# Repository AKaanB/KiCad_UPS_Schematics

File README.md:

# KiCad_UPS_Schematics
 Open Source Schematics of a Li-ion battery based 1.1 KW uninterruptible power supply. Design consists of CC/CV Charger and passive battery balancing and a full bridge inverter.
You can just take a look at the PDF if you only want to see the schematics.

All parts have footprints except the transformers. 
Order list is finished. All parts can be bought from digikey they are included in the table.

This design is NOT tested. I will update it if I can finish it.

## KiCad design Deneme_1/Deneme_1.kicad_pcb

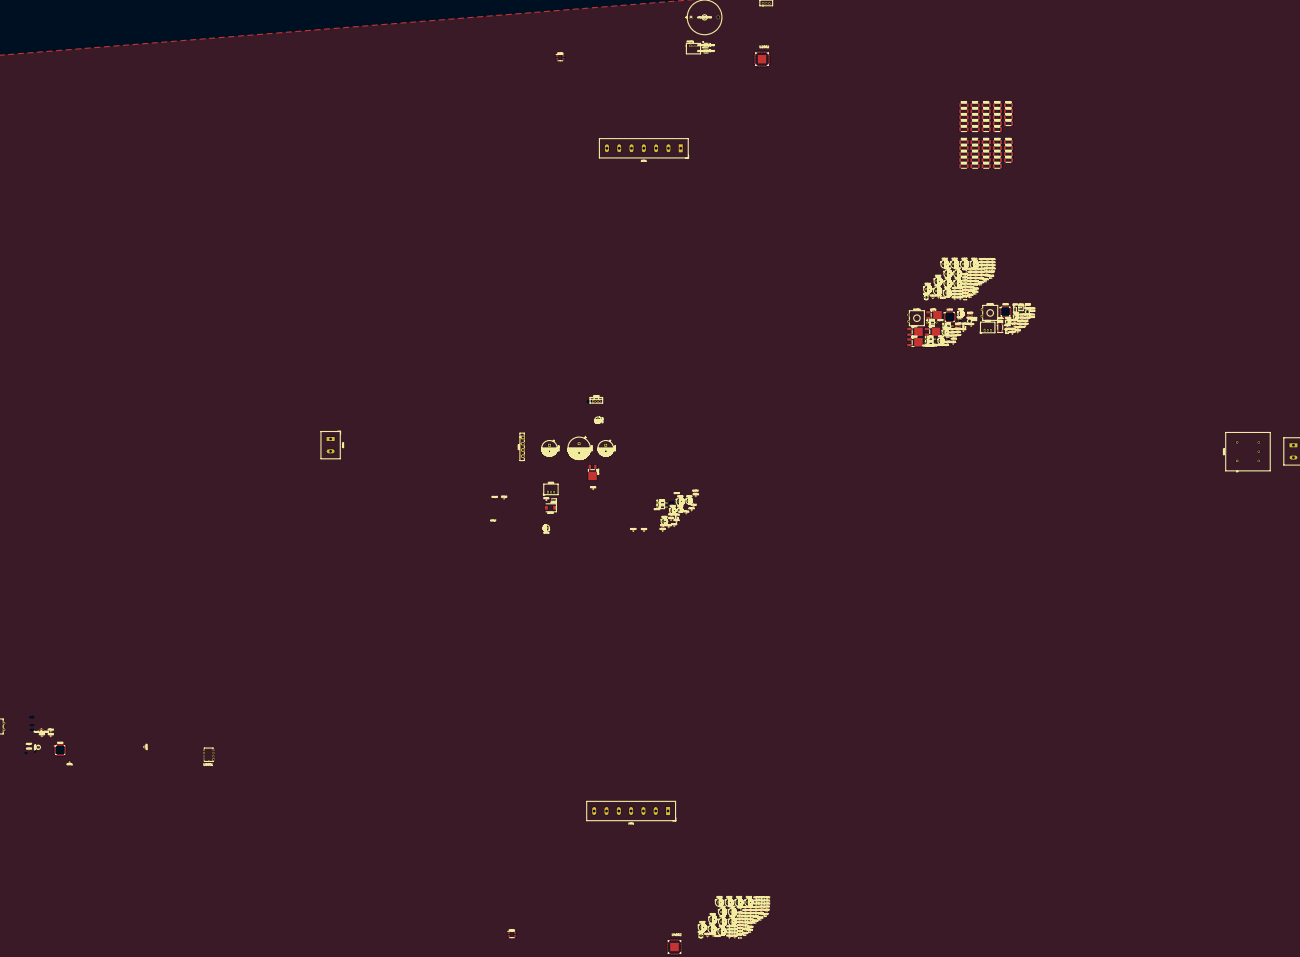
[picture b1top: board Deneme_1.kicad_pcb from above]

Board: 2 copper layers, 329 parts (0 on the bottom side), 230 nets, no tracks yet.

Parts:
C2001, C2002, C4001, C4002: 47nF_16V; C_0603_1608Metric_Pad1.05x0.95mm_HandSolder
C2003, C2007, C2008, C3001, C3007, C4003, C4007, C4008, C5021: 100nF_50V; C_0603_1608Metric_Pad1.05x0.95mm_HandSolder
C2004, C4004: 2uF2_16V; C_0603_1608Metric_Pad1.05x0.95mm_HandSolder
C2005, C4005: 10uF_10V; C_0603_1608Metric_Pad1.05x0.95mm_HandSolder
C2006, C4006: 1nF_10V; C_0603_1608Metric_Pad1.05x0.95mm_HandSolder
C2009, C3010, C3011, C3012, C3013, C3014, C4009, C5001, C5003, C5012, C6001, C6002, C6006: 100nF_10V; C_0603_1608Metric_Pad1.05x0.95mm_HandSolder
C2010, C2011, C4010, C4011: 2uF2_50V; C_0603_1608Metric_Pad1.05x0.95mm_HandSolder
C2012, C2013, C2014, C2015, C2016, C2017, C2018, C2019, C2020, C2021, C2022, C2023, C4012, C4013, C4014, C4015, C4016, C4017, C4018, C4019, C4020, C4021, C4022, C4023: 0.1uF_50V; CP_Radial_D6.3mm_P2.50mm
C3002, C3003: 20p_10V; C_0402_1005Metric
C3004, C3005: 4.7pF_10V; C_0402_1005Metric
C3006: 10uF_10V; CP_Radial_D4.0mm_P1.50mm
C3008: 100n_10V; C_0603_1608Metric_Pad1.05x0.95mm_HandSolder
C3009, C5022: 1uF_50V; CP_Radial_D4.0mm_P1.50mm
C5002, C5010: 4.7u_25V; CP_Radial_D5.0mm_P2.50mm
C5004: 10n_25V; C_0603_1608Metric_Pad1.05x0.95mm_HandSolder
C5005: 27u_50V; CP_Radial_D5.0mm_P2.00mm
C5006, C5007, C6003, C6004: 20pF_10V; C_0402_1005Metric
C5008, C5020, C6005, C6009, C6014, C6015, C6018: 100n_25V; C_0201_0603Metric
C5009: 2m2_63V; CP_Radial_D18.0mm_P7.50mm
C5011, C5013: 470u_63V; CP_Radial_D12.5mm_P5.00mm
C5014, C6010: 10nF_10V; C_0603_1608Metric_Pad1.05x0.95mm_HandSolder
C5015, C6011: 1uF_10V; C_0603_1608Metric_Pad1.05x0.95mm_HandSolder
C5016, C5019: 10u_50V; CP_Radial_D5.0mm_P2.50mm
C5017, C6012: 100n_50V; C_0201_0603Metric
C5018: 47u_50V; CP_Radial_D6.3mm_P2.50mm
C6007, C6016: 10u_25V; CP_Radial_D5.0mm_P2.50mm
C6008, C6017: 47n_25V; C_0402_1005Metric
C6013: 4.7uF_25V; CP_Radial_D5.0mm_P2.50mm
D2001, D4001: LED; LED_D3.0mm
D2002, D2003, D2004, D2005, D2006, D2007, D4002, D4003, D4004, D4005, D4006, D4007: DZ2S051X0L; D_SOD-523
D3001, D5005: MMSZ4685T1G; D_SOD-123
D5001: GBU4B; Diode_Bridge_Vishay_GBU
D5002, D5003, D6001, D6002, D6003, D6004: 1N914; D_DO-35_SOD27_P7.62mm_Horizontal
D5004: S5AC-13-F; D_SMC
FL6001: FN405-10-02; Filter_Schaffner_FN405
Ferrit_Bead5001, Ferrit_Bead6001: R; R_0805_2012Metric_Pad1.15x1.40mm_HandSolder
J2001, J4001: Screw_Terminal_01x07; TerminalBlock_Dinkle_DT-55-B01X-07_P10.00mm
J3001, J5001, J6001: Conn_01x02; PinHeader_1x02_P1.27mm_Vertical
J3002: Conn_02x03_Counter_Clockwise; PinHeader_2x03_P1.27mm_Vertical
J3003: Conn_01x04; PinHeader_1x04_P1.27mm_Vertical
J5002, J6002: Screw_Terminal_01x02; TerminalBlock_Dinkle_DT-55-B01X-02_P10.00mm
L5001: AIRD-03-471K
PS6001: R-78B12-2.0; CONV_R-78B12-2.0
Q2001, Q4001: 2N7002; SOT-23
Q2002, Q2003, Q2004, Q2005, Q2006, Q2007, Q4002, Q4003, Q4004, Q4005, Q4006, Q4007: CSD16301Q2; Texas_DQK
Q5001, Q6001, Q6002, Q6003, Q6004: STD140N6F7; TO-252-2_TabPin1
R2001, R2006, R4001, R4006: 1k47; R_0603_1608Metric_Pad1.05x0.95mm_HandSolder
R2002, R2007, R4002, R4007: 1k82; R_0603_1608Metric_Pad1.05x0.95mm_HandSolder
R2003, R2004, R2005, R2009, R2010, R2011, R2012, R2013, R4003, R4004, R4005, R4009, R4010, R4011, R4012, R4013: 100; R_0603_1608Metric_Pad1.05x0.95mm_HandSolder
R2008, R3004, R3005, R4008: 100k; R_0402_1005Metric
R2014, R4014: 2.7k; R_0805_2012Metric_Pad1.15x1.40mm_HandSolder
R2015, R2016, R2017, R2018, R2019, R2020, R2021, R2022, R2023, R2024, R2025, R2026, R2027, R2028, R2029, R2030, R2031, R2032, R2033, R2034, R2035, R2036, R2037, R2038, R4015, R4016, R4017, R4018, R4019, R4020, R4021, R4022, R4023, R4024, R4025, R4026, R4027, R4028, R4029, R4030, R4031, R4032, R4033, R4034, R4035, R4036, R4037, R4038: 2.2; R_2512_6332Metric_Pad1.52x3.35mm_HandSolder
R2039, R2040, R2041, R2042, R2043, R2044, R3002, R4039, R4040, R4041, R4042, R4043, R4044: 1M; R_0603_1608Metric_Pad1.05x0.95mm_HandSolder
R2045, R2046, R2047, R2048, R2049, R2050, R2051, R2052, R2053, R2054, R2055, R2056, R3006, R3008, R4045, R4046, R4047, R4048, R4049, R4050, R4051, R4052, R4053, R4054, R4055, R4056, R5004, R5006, R5010: 1k; R_0603_1608Metric_Pad1.05x0.95mm_HandSolder
R3001, R5003: 3.3k; R_0805_2012Metric_Pad1.15x1.40mm_HandSolder
R3003, R5002, R5009, R5012, R6002, R6008: 10k; R_0603_1608Metric_Pad1.05x0.95mm_HandSolder
R3007, R3009, R5005, R5007: 2k; R_0805_2012Metric_Pad1.15x1.40mm_HandSolder
R5001, R6001, R6006: 22_2W; R_0603_1608Metric_Pad1.05x0.95mm_HandSolder
R5008, R5014: 33k; R_0603_1608Metric_Pad1.05x0.95mm_HandSolder
R5011: 500k; R_0603_1608Metric_Pad1.05x0.95mm_HandSolder
R5013: 5.6k; R_0402_1005Metric
R5015: 5k; R_0805_2012Metric_Pad1.15x1.40mm_HandSolder
R5016: 910k; R_0603_1608Metric_Pad1.05x0.95mm_HandSolder
R6003, R6005: 100k_5W; R_1210_3225Metric_Pad1.42x2.65mm_HandSolder
R6004, R6007: 10; R_0402_1005Metric
SW3001, SW5001, SW6001: SW_Push; SW_CW_GPTS203211B
TH2001, TH2002, TH4001, TH4002: ERT-J1VG103FA; R_0603_1608Metric_Pad1.05x0.95mm_HandSolder
U2001, U4001: ACS712ELCTR-30A-T; SOIC-8_3.9x4.9mm_P1.27mm
U2002, U4002: BQ76PL536APAPT; QFP50P1200X1200X120-65N
U3001: L7805CV; TO255P1040X460X1968-3
U3002, U5004: R-78C3.3-1.0; Converter_DCDC_RECOM_R-78E-0.5_THT
U3003: STM32F103C8Tx; LQFP-48_7x7mm_P0.5mm
U5001: IR2125PBF; DIP254P762X533-8
U5002, U6003: STM32F031K6Tx; LQFP-32_7x7mm_P0.8mm
U5003: SCD7812BTG; TO-220-3_Vertical
U6001, U6004: LTC7001EMSE#PBF; LTC7001EMSE-PBF
U6002, U6005: MCP1416; SOT-23-5
Y3001, Y5001, Y6001: AB308-8.000MHZ; Crystal_C38-LF_D3.0mm_L8.0mm_Vertical
Y3002: ABS25-32.768KHZ-6-T; Crystal_SMD_Abracon_ABS25-4Pin_8.0x3.8mm

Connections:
1_ADC_1: R5004.1, R5005.2, U5002.6
1_ADC_2: R5006.1, R5007.2, U5002.8
2_ADC_1: R3006.2, R3007.1, U3003.10
2_ADC_2: R3008.2, R3009.1, U3003.11
+BATT_1: C4003.1, C4012.1, D4002.1, J4001.7, R4016.2, R4051.2, U4001.3, U4001.4, U4002.52, U4002.53, U4002.54, U4002.55, U4002.56, U4002.57, U4002.58, U4002.59, U4002.63, U4002.64
+BATT_2: C2003.1, C2012.1, D2002.1, J2001.7, R2016.2, R2051.2, U2001.3, U2001.4, U2002.52, U2002.53, U2002.54, U2002.55, U2002.56, U2002.57, U2002.58, U2002.59, U2002.63, U2002.64
-BATT_1: C2003.2, C2004.2, C2005.2, C2006.2, C2008.2, C2009.2, C2011.2, C2017.2, C2018.2, C2019.2, C2020.2, C2021.2, C2022.2, C2023.2, C3001.2, C3002.2, C3003.2, C3004.2, C3005.2, C3006.2, C3007.2, C3008.1, C3009.2, C4003.2, C4004.2, C4005.2, C4006.2, C4008.2, C4009.2, C4011.2, C4017.2, C4018.2, C4019.2, C4020.2, C4021.2, C4022.2, C4023.2, C5002.2, C5004.2, C5006.1, C5007.1, C5009.2, C5010.2, C5011.2, C5012.2, C5013.2, C5014.2, C5015.2, C5016.2, C5017.2, C5018.2, C5019.2, C5020.2, C5021.2, C5022.2, C6003.1, C6004.1, C6005.2, C6006.2, C6008.2, C6010.2, C6011.2, C6012.2, C6013.2, C6014.2, C6015.2, C6017.2, D2007.2, D3001.2, D4007.2, D5001.4, D5004.2, D5005.2, FL6001.3, J2001.1, J3002.3, J3002.4, J4001.1, PS6001.2, Q2001.2, Q2007.4, Q2007.7, Q4001.2, Q4007.4, Q4007.7, R2044.1, R3001.2, R3007.2, R3009.2, R4044.1, R5003.1, R5005.1, R5007.1, R5010.1, R5013.1, R5015.1, R5016.1, R6002.1, R6008.1, SW3001.2, SW5001.1, SW6001.1, U2001.5, U2002.13, U2002.15, U2002.21, U2002.22, U2002.23, U2002.24, U2002.26, U2002.27, U2002.28, U2002.29, U3001.2, U3002.2, U4001.5, U4002.13, U4002.15, U4002.21, U4002.22, U4002.23, U4002.24, U4002.26, U4002.27, U4002.28, U4002.29, U5001.4, U5002.31, U5003.2, U5004.2, U6001.2, U6001.3, U6001.5, U6002.4, U6003.31, U6004.2, U6004.3, U6004.5, U6005.4
ALERT_H_1: R4010.1, U3003.45
ALERT_H_2: R2010.1, U3003.33
BATT_LOW_HIGH: R3001.1, U3003.12, U6003.14
BOOT0: R3004.2, U3003.44
BOOT1: R3005.2, U3003.20
CB1_1: R4050.1, U4002.12
CB1_2: R2050.1, U2002.12
CB2_1: R4049.1, U4002.10
CB2_2: R2049.1, U2002.10
CB3_1: R4048.1, U4002.8
CB3_2: R2048.1, U2002.8
CB4_1: R4047.1, U4002.6
CB4_2: R2047.1, U2002.6
CB5_1: R4046.1, U4002.4
CB5_2: R2046.1, U2002.4
CB6_1: R4045.1, U4002.2
CB6_2: R2045.1, U2002.2
CC_CV_CHARGER_PWM: U5001.2, U5002.18
CHARGER_12V_DC: C5002.1, C5004.1, C5019.1, C5020.1, D5002.2, U5001.1, U5003.3
CHARGER_VDD_3.3V: C5001.1, C5003.1, C5022.1, D5005.1, Ferrit_Bead5001.2, U5002.1, U5002.17, U5004.3
CS_H_1: R4004.2, U3003.38
CS_H_2: R2004.2, U3003.25
Current_Sense_1: R3006.1, R5004.2, U4001.7
Current_Sense_2: R3008.1, R5006.2, U2001.7
DRDY_H_1: R4009.1, U3003.46
DRDY_H_2: R2009.1, U3003.32
FAULT_H_1: R4012.1, U3003.31
FAULT_H_2: R2012.1, U3003.29
GNDD: C2007.2, C2010.2, C3011.2, C3012.2, C3013.2, C3014.2, C4007.2, C4010.2, C5001.2, C5003.2, C6001.2, C6002.2, J3003.4, U2002.14, U2002.25, U2002.33, U2002.34, U2002.35, U2002.44, U2002.47, U2002.48, U2002.49, U2002.50, U3003.8, U3003.23, U3003.35, U3003.47, U4002.14, U4002.25, U4002.33, U4002.34, U4002.35, U4002.44, U4002.47, U4002.48, U4002.49, U4002.50, U5002.16, U5002.32, U6003.16, U6003.32
I2C_SCL: J3003.2, U3003.21
I2C_SDA: J3003.3, U3003.22
INV_HIGH_SIDE_PWM_1: U6001.4, U6003.18
INV_HIGH_SIDE_PWM_2: U6003.21, U6004.4
INV_LOW_SIDE_PWM_1: U6002.3, U6003.28
INV_LOW_SIDE_PWM_2: U6003.27, U6005.3
Line_On_Off_Digital: R5003.2, U5002.22, U6003.22
NRST: C3008.2, R3003.2, SW3001.1, U3003.7
unnamed: C2001.2, R2001.2, R2002.2, U2002.61
unnamed: C2002.2, R2006.2, R2007.2, U2002.20
unnamed: C2005.1, U2002.16
unnamed: C2006.1, U2001.6
unnamed: C2007.1, C2010.1, U2002.18, U2002.46
unnamed: C2008.1, C2011.1, U2002.17
unnamed: C2012.2, C2013.1, D2002.2, D2003.1, J2001.6, Q2002.4, Q2002.7, R2017.2, R2039.1, R2052.2
unnamed: C2013.2, C2014.1, D2003.2, D2004.1, J2001.5, Q2003.4, Q2003.7, R2018.2, R2040.1, R2053.2
unnamed: C2014.2, C2015.1, D2004.2, D2005.1, J2001.4, Q2004.4, Q2004.7, R2015.2, R2041.1, R2054.2
unnamed: C2015.2, C2016.1, D2005.2, D2006.1, J2001.3, Q2005.4, Q2005.7, R2019.2, R2042.1, R2055.2
unnamed: C2016.2, C2017.1, D2006.2, D2007.1, J2001.2, Q2006.4, Q2006.7, R2020.2, R2043.1, R2056.2
unnamed: C3010.2, U3003.1
unnamed: C4001.2, R4001.2, R4002.2, U4002.61
unnamed: C4002.2, R4006.2, R4007.2, U4002.20
unnamed: C4005.1, U4002.16
unnamed: C4006.1, U4001.6
unnamed: C4007.1, C4010.1, U4002.18, U4002.46
unnamed: C4008.1, C4011.1, U4002.17
unnamed: C4012.2, C4013.1, D4002.2, D4003.1, J4001.6, Q4002.4, Q4002.7, R4017.2, R4039.1, R4052.2
unnamed: C4013.2, C4014.1, D4003.2, D4004.1, J4001.5, Q4003.4, Q4003.7, R4018.2, R4040.1, R4053.2
unnamed: C4014.2, C4015.1, D4004.2, D4005.1, J4001.4, Q4004.4, Q4004.7, R4015.2, R4041.1, R4054.2
unnamed: C4015.2, C4016.1, D4005.2, D4006.1, J4001.3, Q4005.4, Q4005.7, R4019.2, R4042.1, R4055.2
unnamed: C4016.2, C4017.1, D4006.2, D4007.1, J4001.2, Q4006.4, Q4006.7, R4020.2, R4043.1, R4056.2
unnamed: C5005.1, C5008.1, D5002.1, U5001.8
unnamed: C5006.2, U5002.3, Y5001.1
unnamed: C5007.2, U5002.2, Y5001.2
unnamed: C5010.1, U5001.3
unnamed: C5012.1, SW5001.2, U5002.4
unnamed: C5014.1, C5015.1, Ferrit_Bead5001.1, U5002.5
unnamed: C6003.2, U6003.3, Y6001.1
unnamed: C6004.2, U6003.2, Y6001.2
unnamed: C6006.1, SW6001.2, U6003.4
unnamed: C6007.1, C6009.1, D6001.1, U6001.9
unnamed: C6007.2, C6009.2, U6001.8
unnamed: C6008.1, R6004.1
unnamed: C6010.1, C6011.1, Ferrit_Bead6001.1, U6003.5
unnamed: C6016.1, C6018.1, D6003.1, U6004.9
unnamed: C6016.2, C6018.2, U6004.8
unnamed: C6017.1, R6007.1
unnamed: D2001.1, Q2001.3
unnamed: D2001.2, R2014.2
unnamed: D4001.1, Q4001.3
unnamed: D4001.2, R4014.2
unnamed: D5003.1, R5001.2, U5001.7
unnamed: D5003.2, Q5001.1, R5001.1, R5002.1
unnamed: D5004.1, L5001.2, R5002.2
unnamed: D6002.1, R6001.2, U6002.5
unnamed: D6002.2, Q6001.1, R6001.1, R6002.2
unnamed: D6004.1, R6006.2, U6005.5
unnamed: D6004.2, Q6004.1, R6006.1, R6008.2
unnamed: J3002.2, R3004.1
unnamed: J3002.5, R3005.1
unnamed: Q2001.1, R2011.2
unnamed: Q2002.1, Q2002.2, Q2002.5, Q2002.6, Q2002.8, R2022.1
unnamed: Q2002.3, R2039.2, R2045.2
unnamed: Q2003.1, Q2003.2, Q2003.5, Q2003.6, Q2003.8, R2024.1
unnamed: Q2003.3, R2040.2, R2046.2
unnamed: Q2004.1, Q2004.2, Q2004.5, Q2004.6, Q2004.8, R2026.1
unnamed: Q2004.3, R2041.2, R2047.2
unnamed: Q2005.1, Q2005.2, Q2005.5, Q2005.6, Q2005.8, R2028.1
unnamed: Q2005.3, R2042.2, R2048.2
unnamed: Q2006.1, Q2006.2, Q2006.5, Q2006.6, Q2006.8, R2030.1
unnamed: Q2006.3, R2043.2, R2049.2
unnamed: Q2007.1, Q2007.2, Q2007.5, Q2007.6, Q2007.8, R2032.1
unnamed: Q2007.3, R2044.2, R2050.2
unnamed: Q4001.1, R4011.2
unnamed: Q4002.1, Q4002.2, Q4002.5, Q4002.6, Q4002.8, R4022.1
unnamed: Q4002.3, R4039.2, R4045.2
unnamed: Q4003.1, Q4003.2, Q4003.5, Q4003.6, Q4003.8, R4024.1
unnamed: Q4003.3, R4040.2, R4046.2
unnamed: Q4004.1, Q4004.2, Q4004.5, Q4004.6, Q4004.8, R4026.1
unnamed: Q4004.3, R4041.2, R4047.2
unnamed: Q4005.1, Q4005.2, Q4005.5, Q4005.6, Q4005.8, R4028.1
unnamed: Q4005.3, R4042.2, R4048.2
unnamed: Q4006.1, Q4006.2, Q4006.5, Q4006.6, Q4006.8, R4030.1
unnamed: Q4006.3, R4043.2, R4049.2
unnamed: Q4007.1, Q4007.2, Q4007.5, Q4007.6, Q4007.8, R4032.1
unnamed: Q4007.3, R4044.2, R4050.2
unnamed: Q6002.1, R6003.1, R6004.2, U6001.6
unnamed: Q6003.1, R6005.1, R6007.2, U6004.6
unnamed: R2001.1, TH2001.2
unnamed: R2002.1, U2002.60
unnamed: R2003.1, U2002.40
unnamed: R2004.1, U2002.43
unnamed: R2005.1, U2002.42
unnamed: R2006.1, TH2002.2
unnamed: R2007.1, U2002.19
unnamed: R2008.2, R2011.1, U2002.45
unnamed: R2009.2, U2002.37
unnamed: R2010.2, U2002.38
unnamed: R2012.2, U2002.39
unnamed: R2013.2, U2002.41
unnamed: R2015.1, R2027.2
unnamed: R2016.1, R2021.2
unnamed: R2017.1, R2023.2
unnamed: R2018.1, R2025.2
unnamed: R2019.1, R2029.2
unnamed: R2020.1, R2031.2
unnamed: R2021.1, R2033.2
unnamed: R2022.2, R2033.1
unnamed: R2023.1, R2034.2
unnamed: R2024.2, R2034.1
unnamed: R2025.1, R2035.2
unnamed: R2026.2, R2035.1
unnamed: R2027.1, R2036.2
unnamed: R2028.2, R2036.1
unnamed: R2029.1, R2037.2
unnamed: R2030.2, R2037.1
unnamed: R2031.1, R2038.2
unnamed: R2032.2, R2038.1
unnamed: R4001.1, TH4001.2
unnamed: R4002.1, U4002.60
unnamed: R4003.1, U4002.40
unnamed: R4004.1, U4002.43
unnamed: R4005.1, U4002.42
unnamed: R4006.1, TH4002.2
unnamed: R4007.1, U4002.19
unnamed: R4008.2, R4011.1, U4002.45
unnamed: R4009.2, U4002.37
unnamed: R4010.2, U4002.38
unnamed: R4012.2, U4002.39
unnamed: R4013.2, U4002.41
unnamed: R4015.1, R4027.2
unnamed: R4016.1, R4021.2
unnamed: R4017.1, R4023.2
unnamed: R4018.1, R4025.2
unnamed: R4019.1, R4029.2
unnamed: R4020.1, R4031.2
unnamed: R4021.1, R4033.2
unnamed: R4022.2, R4033.1
unnamed: R4023.1, R4034.2
unnamed: R4024.2, R4034.1
unnamed: R4025.1, R4035.2
unnamed: R4026.2, R4035.1
unnamed: R4027.1, R4036.2
unnamed: R4028.2, R4036.1
unnamed: R4029.1, R4037.2
unnamed: R4030.2, R4037.1
unnamed: R4031.1, R4038.2
unnamed: R4032.2, R4038.1
unnamed: R5009.1, R5010.2
unnamed: R5011.1, R5012.2
unnamed: R5012.1, R5013.2
unnamed: R6003.2, U6001.7
unnamed: R6005.2, U6004.7
OSC32_IN: C3004.1, U3003.3, Y3002.1
OSC32_OUT: C3005.1, U3003.4, Y3002.4
OSCIN: C3002.1, R3002.1, U3003.5, Y3001.1
OSCOUT: C3003.1, R3002.2, U3003.6, Y3001.2
OUTPUT_AC_1: FL6001.4, J6002.1
OUTPUT_AC_2: FL6001.2, J6002.2
REG50_1: C4001.1, C4002.1, C4004.1, R4008.1, R4014.1, TH4001.1, TH4002.1, U4002.32
REG50_2: C2001.1, C2002.1, C2004.1, R2008.1, R2014.1, TH2001.1, TH2002.1, U2002.32
SCLK_H_1: R4003.2, U3003.39
SCLK_H_2: R2003.2, U3003.26
SDI_H_1: R4005.2, U3003.41
SDI_H_2: R2005.2, U3003.28
SDO_H_1: R4013.1, U3003.40
SDO_H_2: R2013.1, U3003.27
SWCLK_1: J5001.2, U5002.24
SWCLK_2: J3001.2, U3003.37
SWCLK_3: J6001.2, U6003.24
SWDIO_1: J5001.1, U5002.23
SWDIO_2: J3001.1, U3003.34
SWDIO_3: J6001.1, U6003.23
Transformer_AC_Output_1: FL6001.5, J5002.1
Transformer_AC_Output_2: FL6001.1, J5002.2
VC1_1: C4023.1, R4056.1, U4002.11
VC1_2: C2023.1, R2056.1, U2002.11
VC2_1: C4022.1, R4055.1, U4002.9
VC2_2: C2022.1, R2055.1, U2002.9
VC3_1: C4021.1, R4054.1, U4002.7
VC3_2: C2021.1, R2054.1, U2002.7
VC4_1: C4020.1, R4053.1, U4002.5
VC4_2: C2020.1, R2053.1, U2002.5
VC5_1: C4019.1, R4052.1, U4002.3
VC5_2: C2019.1, R2052.1, U2002.3
VC6_1: C4018.1, R4051.1, U4002.1
VC6_2: C2018.1, R2051.1, U2002.1
VDD_3.3V: C3009.1, C3010.1, C3011.1, C3012.1, C3013.1, C3014.1, C6001.1, C6002.1, D3001.1, Ferrit_Bead6001.2, J3002.1, J3002.6, R3003.1, U3002.3, U3003.9, U3003.24, U3003.36, U3003.48, U6003.1, U6003.17
VDD_5V: C2009.1, C3006.1, C4009.1, J3003.1, U2001.8, U3001.3, U4001.8
V_BUS: C3001.1, C3007.1, C5005.2, C5008.2, C5018.1, C6012.1, L5001.1, PS6001.1, Q6002.2, Q6003.2, R5014.2, U2001.1, U2001.2, U3001.1, U3002.1, U4001.1, U4001.2, U5001.5, U5001.6
V_BUS_12V_DC: C6005.1, C6013.1, C6014.1, C6015.1, D6001.2, D6003.2, PS6001.3, U6001.1, U6002.2, U6004.1, U6005.2
V_BUS_ADC: R5014.1, R5015.2, R5016.2, U5002.7
V_RECTIFIED_DC: C5009.1, C5011.1, C5013.1, C5016.1, C5017.1, C5021.1, D5001.1, Q5001.2, R5008.2, U5003.1, U5004.1
V_RECTIFIED_DC_ADC: R5008.1, R5009.2, R5011.2, U5002.9

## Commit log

2020-08-13 Update 00

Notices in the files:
parts and their libraries:
Copyright 2016 Accelerated Designs. All rights reserved.
